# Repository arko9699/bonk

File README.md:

# bonk
A 13u "WKL-like" row-staggered keyboard using MX switches and STM32F072 microcontroller, running QMK firmware.
 
* Support for uDB or use the USB-C connector on the board [WARNING: Do not use both at the same time]
* Cutouts for Gummy O-ring mounts
* ISO/ANSI Enter [added in rev2]

# Pics

# Building 
If you want to get a few of these PCBs to build yourself or share with friends, head over to "Releases" and download the latest gerber files. Order from any PCB manufacturer of your choice however the included BOM and CPL are tailored for JLCPCB. A hot plate or hot air station is recommended to solder components yourself. 
NOTE : For cost saving, either the JST connector OR the USB-C and related components may be omitted from the BOM.

# Changelog
* rev2
  - Expanded layout options including ISO Enter, more flexible Split Left Shift, new 3u spacebar option. 7u spacebar layout has been removed due to lack of usability and its presence as more of a gimmick.
* rev1.1
  - Changed reset/boot circuitry. Now there is only one button for both actions. Hold the buttom for ~30s to enter the bootloader for flashing, or quickly press and release to reset the board. Thanks to the [Acheron Project](https://acheronproject.com/reset_article_1/reset_article_1/) by Gondolindrim and others. This change adds additional components to the BoM but requires less than $1 extra for all parts.
  - Added new compiled firmware which enables a few more QMK features. This is backwards compatible with the older revision of the board.
* rev1.0
  - Initial release

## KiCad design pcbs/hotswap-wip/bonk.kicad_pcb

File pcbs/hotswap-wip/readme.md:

# Flashing

The following steps assume you have a PCB and the latest firmware downloaded

 Steps:
1. Plug in the PCB to the computer using an USB cable (either using uDB or directly)
2. Hold down button for approximately 10 seconds to enter bootloader.
3. Use [QMK Toolbox](https://qmk.fm/toolbox) on [Windows/Mac](https://docs.qmk.fm/newbs_flashing#flashing-your-keyboard-with-qmk-toolbox). Only CLI method is supported on [Linux](https://docs.qmk.fm/flashing#stm32-apm32-dfu).
4. The PCB should restart automatically after flashing and be ready to use.
5. Open [vial](https://vial.rocks/) in a USB HID supported browser (Chrome/Edge/Brave/Opera GX/Other Chromium based browsers) to modify your keymap.

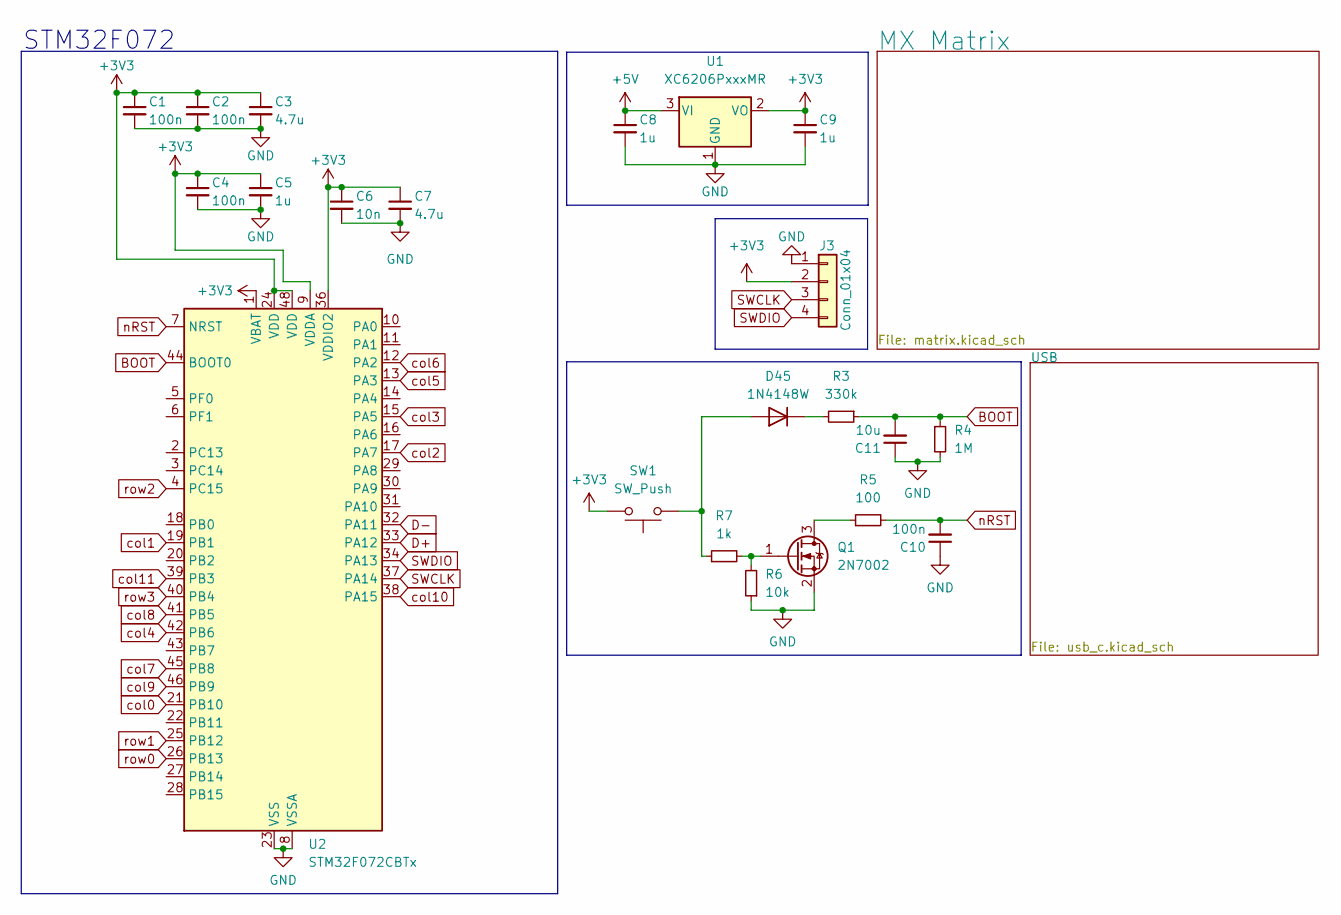
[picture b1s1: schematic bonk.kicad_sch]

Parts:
C1, C2, C4, C10: 100n; C_0402_1005Metric
C3, C7: 4.7u; C_0603_1608Metric
C5, C8, C9: 1u; C_0603_1608Metric
C6: 10n; C_0402_1005Metric
C11: 10u; C_0603_1608Metric
D45: 1N4148W; D_SOD-123
J3: Conn_01x04; PinHeader_2x02_P2.54mm_Vertical
Q1: 2N7002; SOT-23
R3: 330k; R_0805_2012Metric
R4: 1M; R_0805_2012Metric
R5: 100; R_0402_1005Metric
R6: 10k; R_0603_1608Metric
R7: 1k; R_0603_1608Metric
SW1: SW_Push; SW_Push_1P1T_XKB_TS-1187A
U1: XC6206PxxxMR; SOT-23-3
U2: STM32F072CBTx; LQFP-48_7x7mm_P0.5mm

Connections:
+3V3: C1.1, C2.1, C3.1, C4.1, C5.1, C6.1, C7.1, C9.1, J3.2, SW1.2, U1.2 (VO), U2.1 (VBAT), U2.9 (VDDA), U2.24 (VDD), U2.36 (VDDIO2), U2.48 (VDD)
+5V: C8.1, U1.3 (VI); also elsewhere on the board
BOOT: C11.2, R3.1, R4.1, U2.44 (BOOT0)
D+: U2.33 (PA12); also elsewhere on the board
D-: U2.32 (PA11); also elsewhere on the board
GND: C1.2, C2.2, C3.2, C4.2, C5.2, C6.2, C7.2, C8.2, C9.2, C10.1, C11.1, J3.1, Q1.2 (S), R4.2, R6.1, U1.1 (GND), U2.8 (VSSA), U2.23 (VSS), U2.35 (VSS), U2.47 (VSS); also elsewhere on the board
unnamed: D45.2 (A), R7.1, SW1.1
unnamed: D45.1 (K), R3.2
unnamed: Q1.3 (D), R5.1
unnamed: Q1.1 (G), R6.2, R7.2
SWCLK: J3.3, U2.37 (PA14)
SWDIO: J3.4, U2.34 (PA13)
col0: U2.21 (PB10); also elsewhere on the board
col1: U2.19 (PB1); also elsewhere on the board
col2: U2.17 (PA7); also elsewhere on the board
col3: U2.15 (PA5); also elsewhere on the board
col4: U2.42 (PB6); also elsewhere on the board
col5: U2.13 (PA3); also elsewhere on the board
col6: U2.12 (PA2); also elsewhere on the board
col7: U2.45 (PB8); also elsewhere on the board
col8: U2.41 (PB5); also elsewhere on the board
col9: U2.46 (PB9); also elsewhere on the board
col10: U2.38 (PA15); also elsewhere on the board
col11: U2.39 (PB3); also elsewhere on the board
nRST: C10.2, R5.2, U2.7 (NRST)
row0: U2.26 (PB13); also elsewhere on the board
row1: U2.25 (PB12); also elsewhere on the board
row2: U2.4 (PC15); also elsewhere on the board
row3: U2.40 (PB4); also elsewhere on the board

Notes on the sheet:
STM32F072

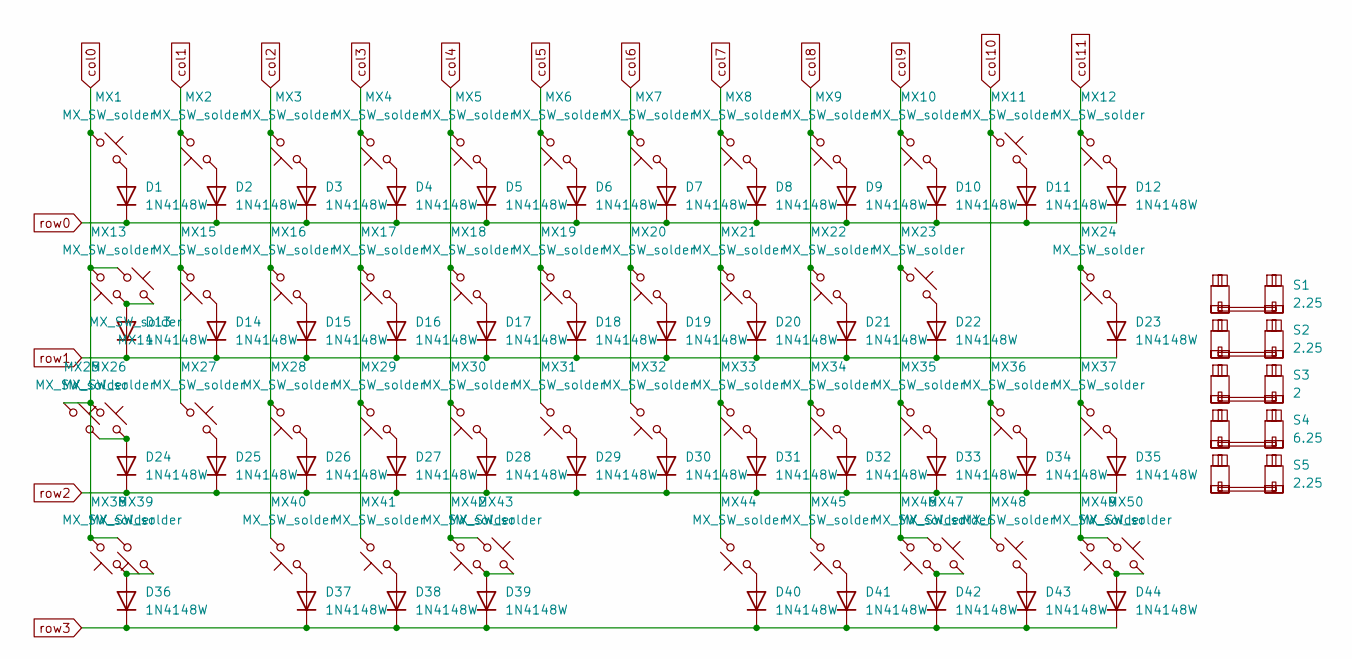
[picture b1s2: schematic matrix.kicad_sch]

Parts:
D1, D2, D3, D4, D5, D6, D7, D8, D9, D10, D11, D12, D13, D14, D15, D16, D17, D18, D19, D20, D21, D22, D23, D24, D25, D26, D27, D28, D29, D30, D31, D32, D33, D34, D35, D36, D37, D38, D39, D40, D41, D42, D43, D44: 1N4148W; D_SOD-123
MX1, MX12: MX_SW_solder; SW_MX_HS_CPG151101S11_1.5u
MX2, MX3, MX4, MX5, MX6, MX7, MX8, MX9, MX10, MX11, MX15, MX16, MX17, MX18, MX19, MX20, MX21, MX22, MX23, MX24, MX25, MX26, MX28, MX29, MX30, MX31, MX32, MX33, MX34, MX35, MX37, MX40, MX42, MX43, MX44, MX45, MX47, MX48: MX_SW_solder; SW_MX_HS_CPG151101S11_1u
MX13, MX36: MX_SW_solder; SW_MX_HS_CPG151101S11_1.75u
MX14: MX_SW_solder; SW_MX_HS_CPG151101S11_1.75u_STP_1.25
MX27, MX38, MX39, MX41, MX46, MX49, MX50: MX_SW_solder; SW_MX_HS_CPG151101S11_1.25u
S1, S2, S5: 2.25; STAB_MX_2.25u
S3: 2; STAB_MX_2u
S4: 6.25; STAB_MX_6.25u

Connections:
unnamed: D1.2 (A), MX1.2
unnamed: D2.2 (A), MX2.1
unnamed: D3.2 (A), MX3.1
unnamed: D4.2 (A), MX4.1
unnamed: D5.2 (A), MX5.1
unnamed: D6.2 (A), MX6.1
unnamed: D7.2 (A), MX7.1
unnamed: D8.2 (A), MX8.1
unnamed: D9.2 (A), MX9.1
unnamed: D10.2 (A), MX10.1
unnamed: D11.2 (A), MX11.2
unnamed: D12.2 (A), MX12.1
unnamed: D13.2 (A), MX13.1, MX14.2
unnamed: D14.2 (A), MX15.1
unnamed: D15.2 (A), MX16.1
unnamed: D16.2 (A), MX17.1
unnamed: D17.2 (A), MX18.1
unnamed: D18.2 (A), MX19.1
unnamed: D19.2 (A), MX20.1
unnamed: D20.2 (A), MX21.1
unnamed: D21.2 (A), MX22.1
unnamed: D22.2 (A), MX23.2
unnamed: D23.2 (A), MX24.1
unnamed: D24.2 (A), MX25.2, MX26.2
unnamed: D25.2 (A), MX27.2
unnamed: D26.2 (A), MX28.1
unnamed: D27.2 (A), MX29.1
unnamed: D28.2 (A), MX30.1
unnamed: D29.2 (A), MX31.1
unnamed: D30.2 (A), MX32.1
unnamed: D31.2 (A), MX33.1
unnamed: D32.2 (A), MX34.1
unnamed: D33.2 (A), MX35.1
unnamed: D34.2 (A), MX36.1
unnamed: D35.2 (A), MX37.1
unnamed: D36.2 (A), MX38.1, MX39.1
unnamed: D37.2 (A), MX40.1
unnamed: D38.2 (A), MX41.1
unnamed: D39.2 (A), MX42.1, MX43.2
unnamed: D40.2 (A), MX44.1
unnamed: D41.2 (A), MX45.1
unnamed: D42.2 (A), MX46.1, MX47.2
unnamed: D43.2 (A), MX48.2
unnamed: D44.2 (A), MX49.1, MX50.2
col0: MX1.1, MX13.2, MX14.1, MX25.1, MX26.1, MX38.2, MX39.2; also elsewhere on the board
col1: MX2.2, MX15.2, MX27.1; also elsewhere on the board
col2: MX3.2, MX16.2, MX28.2, MX40.2; also elsewhere on the board
col3: MX4.2, MX17.2, MX29.2, MX41.2; also elsewhere on the board
col4: MX5.2, MX18.2, MX30.2, MX42.2, MX43.1; also elsewhere on the board
col5: MX6.2, MX19.2, MX31.2; also elsewhere on the board
col6: MX7.2, MX20.2, MX32.2; also elsewhere on the board
col7: MX8.2, MX21.2, MX33.2, MX44.2; also elsewhere on the board
col8: MX9.2, MX22.2, MX34.2, MX45.2; also elsewhere on the board
col9: MX10.2, MX23.1, MX35.2, MX46.2, MX47.1; also elsewhere on the board
col10: MX11.1, MX36.2, MX48.1; also elsewhere on the board
col11: MX12.2, MX24.2, MX37.2, MX49.2, MX50.1; also elsewhere on the board
row0: D1.1 (K), D2.1 (K), D3.1 (K), D4.1 (K), D5.1 (K), D6.1 (K), D7.1 (K), D8.1 (K), D9.1 (K), D10.1 (K), D11.1 (K), D12.1 (K); also elsewhere on the board
row1: D13.1 (K), D14.1 (K), D15.1 (K), D16.1 (K), D17.1 (K), D18.1 (K), D19.1 (K), D20.1 (K), D21.1 (K), D22.1 (K), D23.1 (K); also elsewhere on the board
row2: D24.1 (K), D25.1 (K), D26.1 (K), D27.1 (K), D28.1 (K), D29.1 (K), D30.1 (K), D31.1 (K), D32.1 (K), D33.1 (K), D34.1 (K), D35.1 (K); also elsewhere on the board
row3: D36.1 (K), D37.1 (K), D38.1 (K), D39.1 (K), D40.1 (K), D41.1 (K), D42.1 (K), D43.1 (K), D44.1 (K); also elsewhere on the board

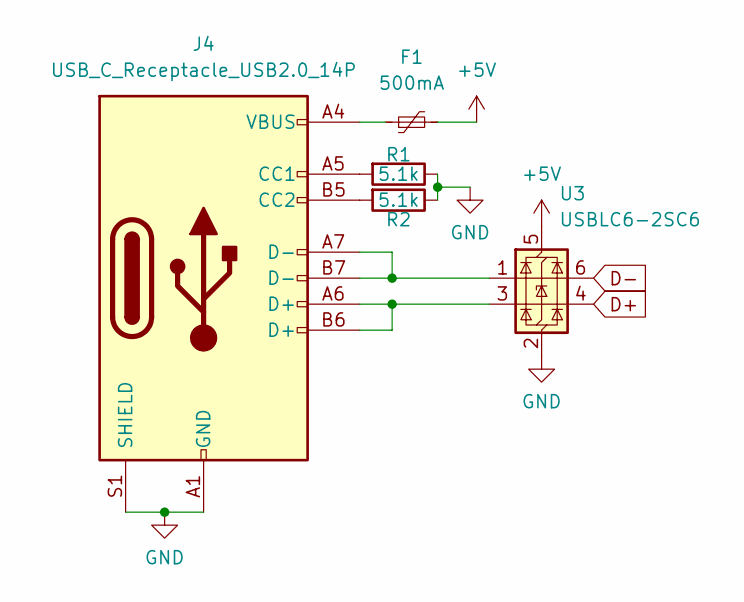
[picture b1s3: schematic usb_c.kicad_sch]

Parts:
F1: 500mA; Fuse_0805_2012Metric
J4: USB_C_Receptacle_USB2.0_14P; USB_C_Receptacle_G-Switch_GT-USB-7010ASV
R1, R2: 5.1k; R_0603_1608Metric
U3: USBLC6-2SC6; SOT-23-6

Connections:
+5V: F1.2, U3.5 (VBUS); also elsewhere on the board
D+: U3.4 (I/O2); also elsewhere on the board
D-: U3.6 (I/O1); also elsewhere on the board
GND: J4.A1 (GND), J4.A12 (GND), J4.B1 (GND), J4.B12 (GND), J4.S1 (SHIELD), R1.1, R2.1, U3.2 (GND); also elsewhere on the board
unnamed: F1.1, J4.A4 (VBUS), J4.A9 (VBUS), J4.B4 (VBUS), J4.B9 (VBUS)
unnamed: J4.A5 (CC1), R1.2
unnamed: J4.B5 (CC2), R2.2
unnamed: J4.A6 (D+), J4.B6 (D+), U3.3 (I/O2)
unnamed: J4.A7 (D-), J4.B7 (D-), U3.1 (I/O1)

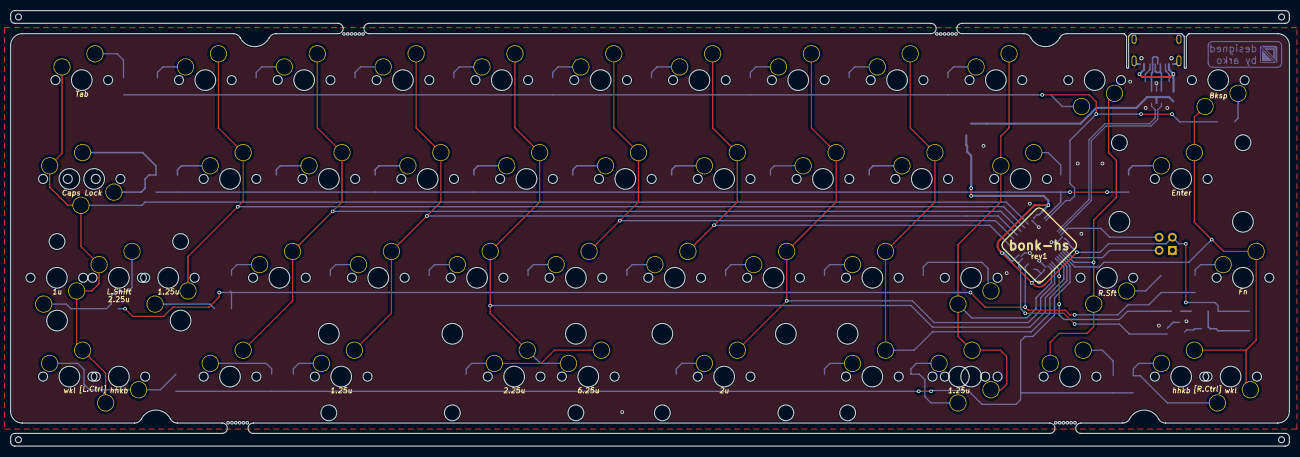
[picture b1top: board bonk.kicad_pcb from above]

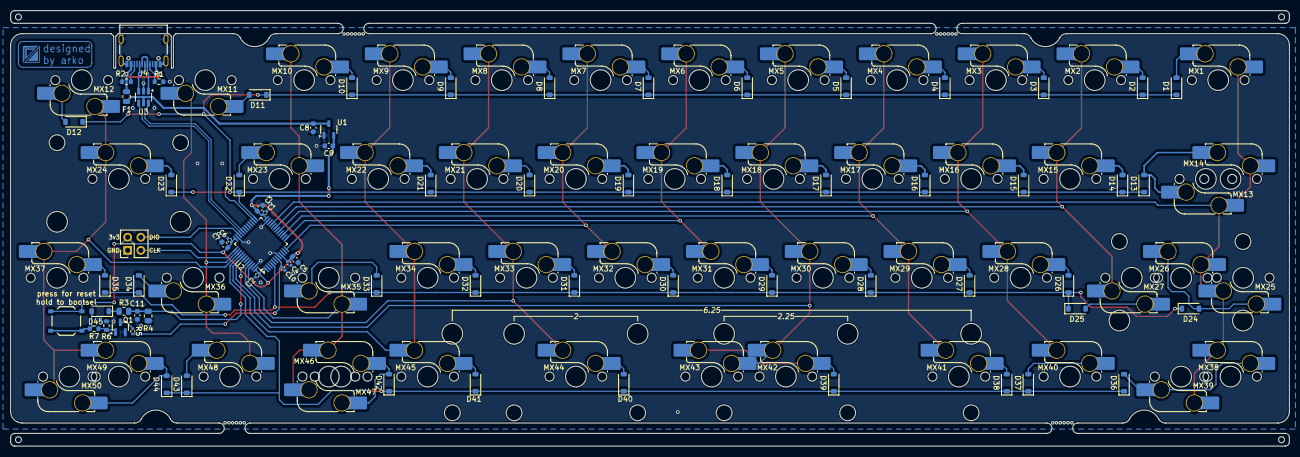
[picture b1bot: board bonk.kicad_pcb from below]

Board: 2 copper layers, 246.5 x 83.9 mm, 126 parts (121 on the bottom side), 78 nets.

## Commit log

2024-10-30 rev1
2024-10-30 rev1.1
2024-10-30 updated image
2024-10-30 added prod files
2024-10-30 renamed directory
2024-11-19 rev01
2024-11-20 rev01a
    added mousebites near usb connector to make removal easier (this is a destructive operation!)
    repositioned usb components to reduce number of vias and add space for mousebites
2024-12-02 Change USB Connector
2024-12-09 Added reference plate file.
2024-12-10 Added layout image
2024-12-10 Fixed keymap, layout image
2024-12-21 case_v1
2024-12-23 Added Part Name for USB connector
2025-01-10 Showcase & keymap change
2025-01-10 Added showcase pics to README
2025-01-12 moar pics
2025-01-16 aesthetic fixes to bonk-pla-case
2025-01-27 rev1.1
    1. Changed reset/boot circuitry to have single-button Reset/Boot functionality.
    2. Removed mounting holes
2025-01-27 Updated firmware
2025-02-10 restructure of files
    moved around files in accordance with logical placements. no new files were added neither older files were removed.
2025-10-19 rev2 and hs-wip
    Restructured file paths and added pcb files for rev2
2025-10-19 Updated readmes and added images
2025-10-22 Updated case files for R2
2025-11-09 Added 2u stab mount points for 3u Spacebar option
2025-12-01 WIP of a wireless, hotswap edition of the bonk
2025-12-07 removed due to lack of personal interest
